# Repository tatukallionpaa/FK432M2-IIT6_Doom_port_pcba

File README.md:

Kicad project files for STM32 doom port. Software repo in https://github.com/tatukallionpaa/stm32_h743_doom_port.

Based on FK743M2-IIT6 dev board. Video is outputted via VGA and a USB keyboard is used as an input.

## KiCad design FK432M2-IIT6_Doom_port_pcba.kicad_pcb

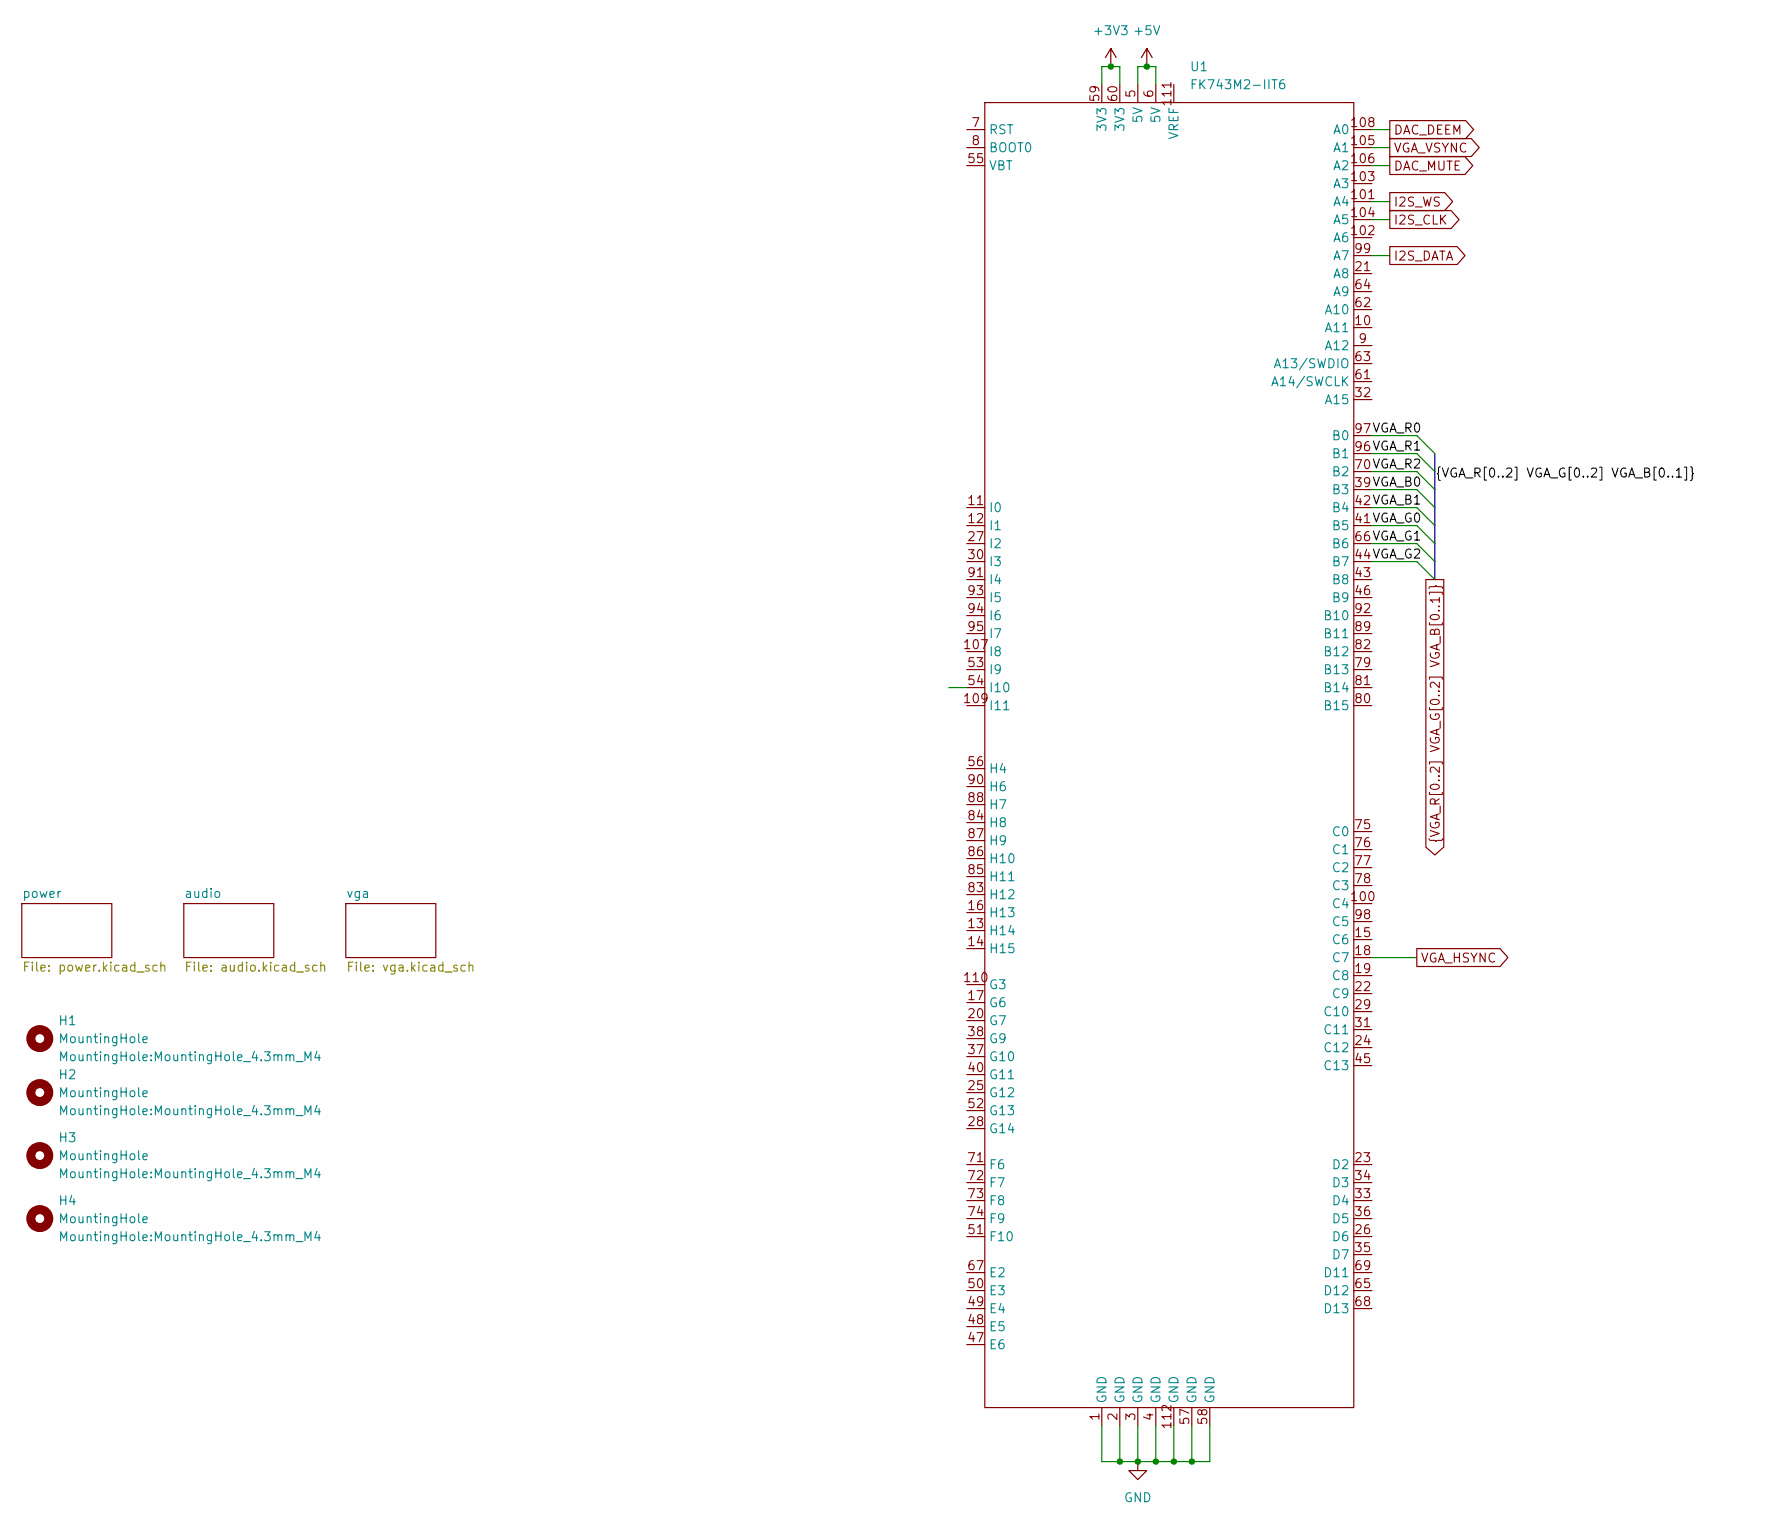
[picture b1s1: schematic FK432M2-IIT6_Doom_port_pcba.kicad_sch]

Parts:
H1, H2, H3, H4: MountingHole; MountingHole_4.3mm_M4
U1: FK743M2-IIT6; FK432M2-IIT6

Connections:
+3V3: U1.59 (3V3), U1.60 (3V3); also elsewhere on the board
+5V: U1.5 (5V), U1.6 (5V); also elsewhere on the board
DAC_DEEM: U1.108 (A0); also elsewhere on the board
DAC_MUTE: U1.106 (A2); also elsewhere on the board
GND: U1.1 (GND), U1.2 (GND), U1.3 (GND), U1.4 (GND), U1.57 (GND), U1.58 (GND), U1.112 (GND); also elsewhere on the board
I2S_CLK: U1.104 (A5); also elsewhere on the board
I2S_DATA: U1.99 (A7); also elsewhere on the board
I2S_WS: U1.101 (A4); also elsewhere on the board
VGA_B0: U1.39 (B3); also elsewhere on the board
VGA_B1: U1.42 (B4); also elsewhere on the board
VGA_G0: U1.41 (B5); also elsewhere on the board
VGA_G1: U1.66 (B6); also elsewhere on the board
VGA_G2: U1.44 (B7); also elsewhere on the board
VGA_HSYNC: U1.18 (C7); also elsewhere on the board
VGA_R0: U1.97 (B0); also elsewhere on the board
VGA_R1: U1.96 (B1); also elsewhere on the board
VGA_R2: U1.70 (B2); also elsewhere on the board
VGA_VSYNC: U1.105 (A1); also elsewhere on the board

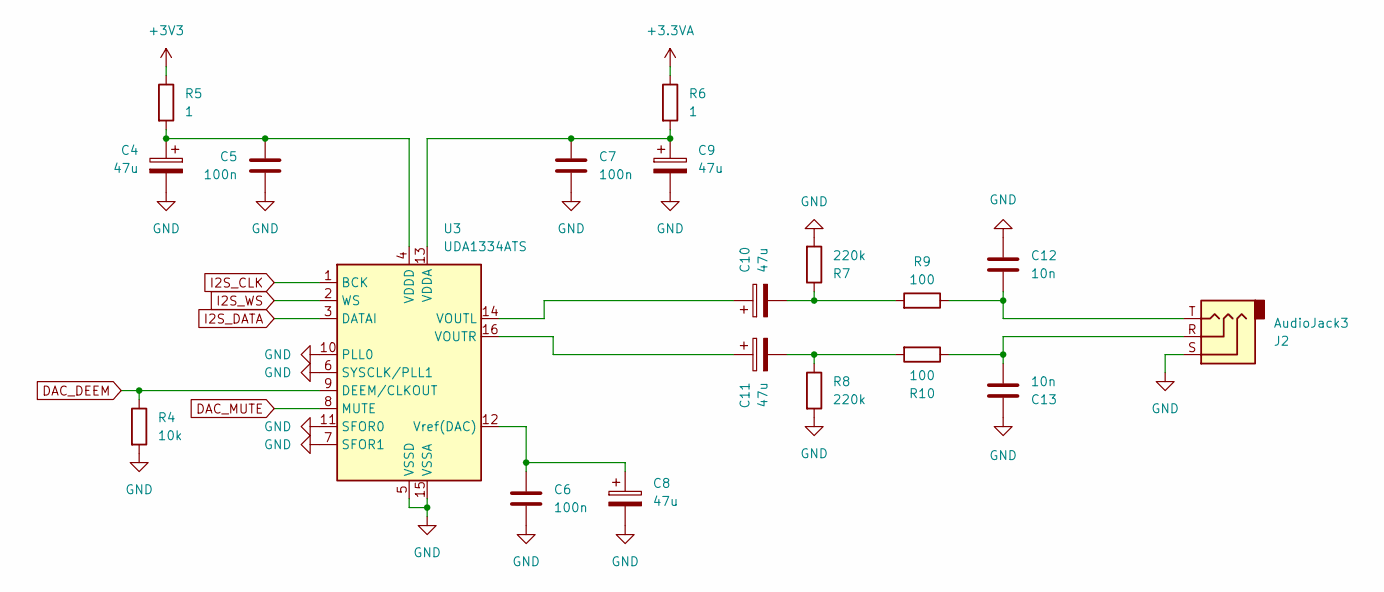
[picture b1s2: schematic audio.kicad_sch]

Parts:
C4, C8, C9, C10, C11: 47u; CP_Elec_5x5.4
C5, C6, C7: 100n; C_0805_2012Metric_Pad1.18x1.45mm_HandSolder
C12, C13: 10n; C_0805_2012Metric_Pad1.18x1.45mm_HandSolder
J2: AudioJack3; Jack_3.5mm_Lumberg_1503_07_Horizontal
R4: 10k; R_0805_2012Metric_Pad1.20x1.40mm_HandSolder
R5, R6: 1; R_0805_2012Metric_Pad1.20x1.40mm_HandSolder
R7, R8: 220k; R_0805_2012Metric_Pad1.20x1.40mm_HandSolder
R9, R10: 100; R_0805_2012Metric_Pad1.20x1.40mm_HandSolder
U3: UDA1334ATS; SSOP-16_4.4x5.2mm_P0.65mm

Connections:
+3.3VA: R6.1; also elsewhere on the board
+3V3: R5.1; also elsewhere on the board
DAC_DEEM: R4.1, U3.9 (DEEM/CLKOUT); also elsewhere on the board
DAC_MUTE: U3.8 (MUTE); also elsewhere on the board
GND: C4.2, C5.2, C6.2, C7.2, C8.2, C9.2, C12.1, C13.1, J2.S, R4.2, R7.2, R8.2, U3.5 (VSSD), U3.6 (SYSCLK/PLL1), U3.7 (SFOR1), U3.10 (PLL0), U3.11 (SFOR0), U3.15 (VSSA); also elsewhere on the board
I2S_CLK: U3.1 (BCK); also elsewhere on the board
I2S_DATA: U3.3 (DATAI); also elsewhere on the board
I2S_WS: U3.2 (WS); also elsewhere on the board
unnamed: C10.2, R7.1, R9.2
unnamed: C11.2, R8.1, R10.2
unnamed: C12.2, J2.T, R9.1
unnamed: C13.2, J2.R, R10.1
unnamed: C7.1, C9.1, R6.2, U3.13 (VDDA)
unnamed: C4.1, C5.1, R5.2, U3.4 (VDDD)
unnamed: C10.1, U3.14 (VOUTL)
unnamed: C11.1, U3.16 (VOUTR)
unnamed: C6.1, C8.1, U3.12 (Vref(DAC))

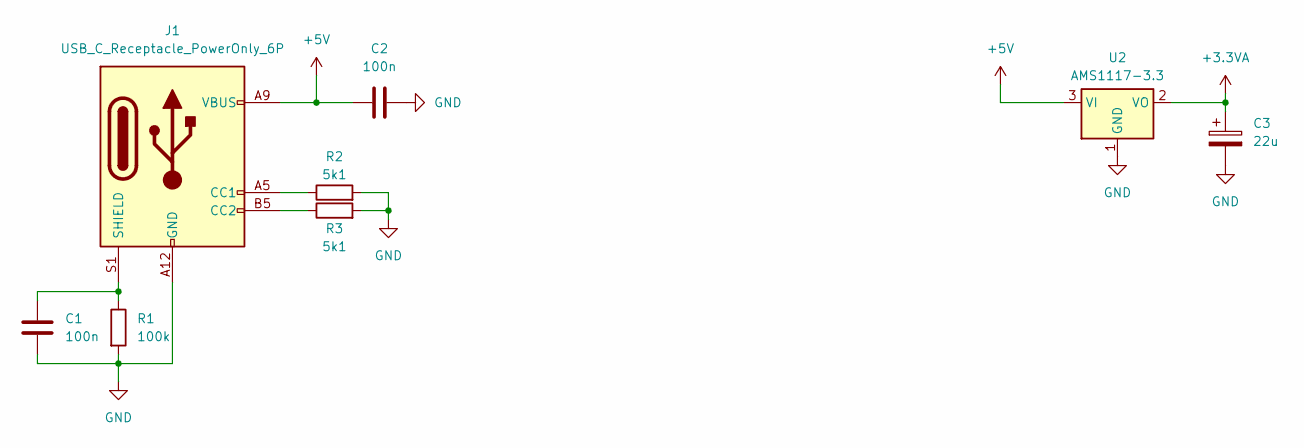
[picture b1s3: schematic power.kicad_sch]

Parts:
C1, C2: 100n; C_0805_2012Metric_Pad1.18x1.45mm_HandSolder
C3: 22u; CP_Elec_4x5.4
J1: USB_C_Receptacle_PowerOnly_6P; USB_C_Receptacle_GCT_USB4125-xx-x_6P_TopMnt_Horizontal
R1: 100k; R_0805_2012Metric_Pad1.20x1.40mm_HandSolder
R2, R3: 5k1; R_0805_2012Metric_Pad1.20x1.40mm_HandSolder
U2: AMS1117-3.3; SOT-223-3_TabPin2

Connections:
+3.3VA: C3.1, U2.2 (VO); also elsewhere on the board
+5V: C2.1, J1.A9 (VBUS), J1.B9 (VBUS), U2.3 (VI); also elsewhere on the board
GND: C1.2, C2.2, C3.2, J1.A12 (GND), J1.B12 (GND), R1.2, R2.2, R3.2, U2.1 (GND); also elsewhere on the board
unnamed: J1.A5 (CC1), R2.1
unnamed: J1.B5 (CC2), R3.1
unnamed: C1.1, J1.S1 (SHIELD), R1.1

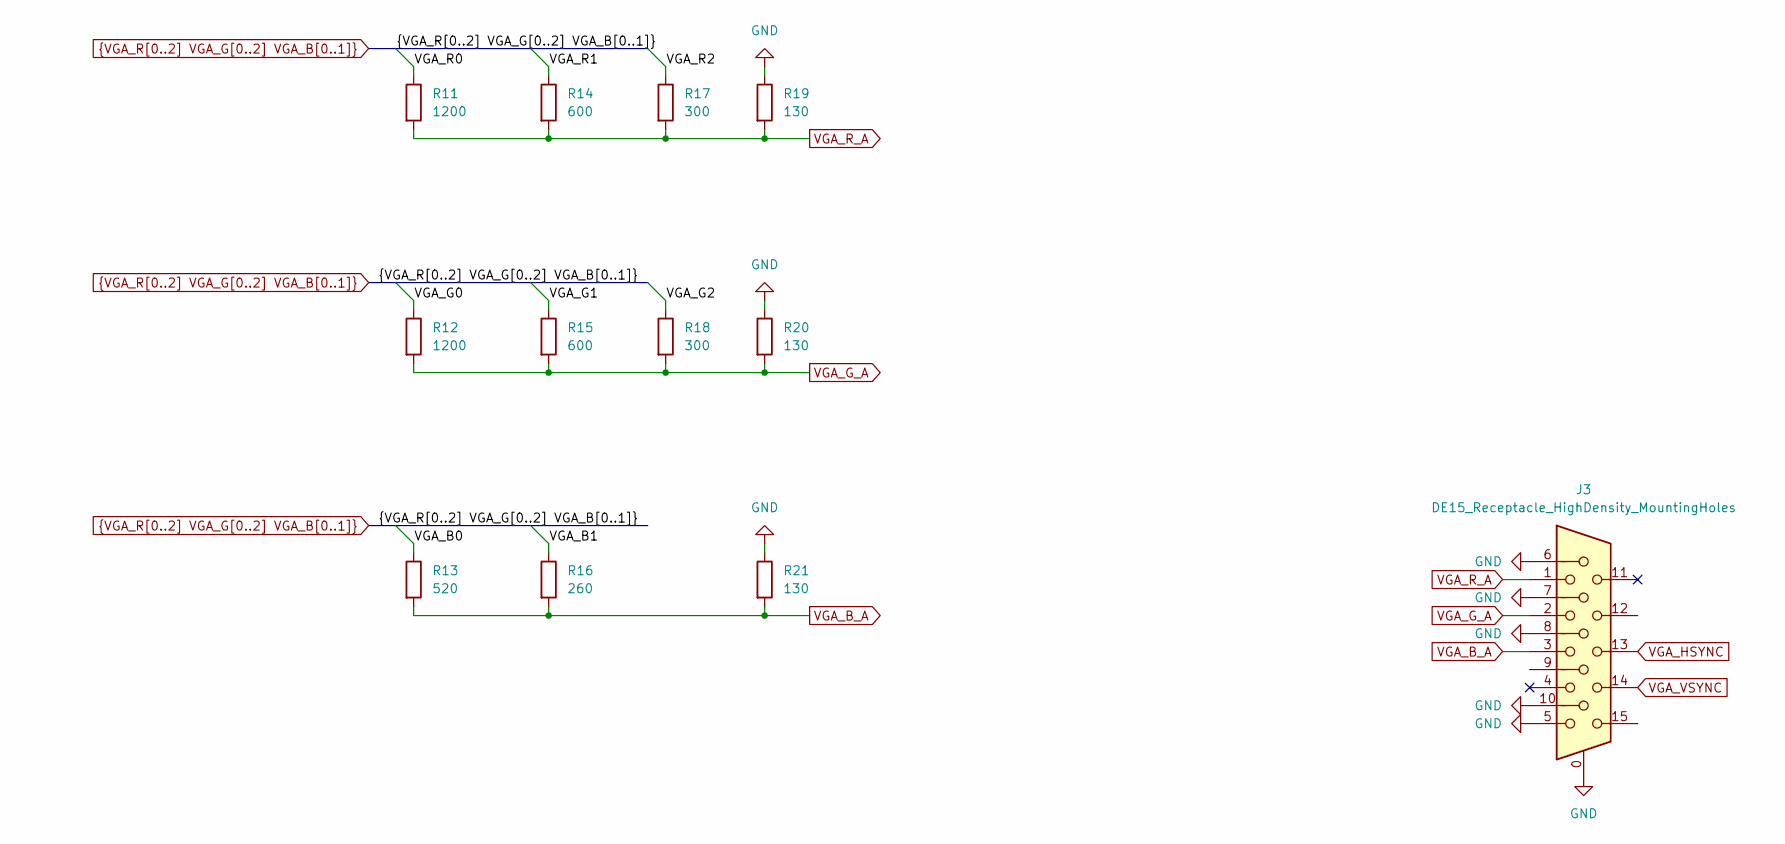
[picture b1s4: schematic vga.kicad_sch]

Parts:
J3: DE15_Receptacle_HighDensity_MountingHoles; DSUB-15-HD_Female_Horizontal_P2.29x1.98mm_EdgePinOffset3.03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
R11, R12: 1200; R_0805_2012Metric_Pad1.20x1.40mm_HandSolder
R13: 520; R_0805_2012Metric_Pad1.20x1.40mm_HandSolder
R14, R15: 600; R_0805_2012Metric_Pad1.20x1.40mm_HandSolder
R16: 260; R_0805_2012Metric_Pad1.20x1.40mm_HandSolder
R17, R18: 300; R_0805_2012Metric_Pad1.20x1.40mm_HandSolder
R19, R20, R21: 130; R_0805_2012Metric_Pad1.20x1.40mm_HandSolder

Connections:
GND: J3.0, J3.5, J3.6, J3.7, J3.8, J3.10, R19.1, R20.1, R21.1; also elsewhere on the board
VGA_B0: R13.1; also elsewhere on the board
VGA_B1: R16.1; also elsewhere on the board
VGA_B_A: J3.3, R13.2, R16.2, R21.2
VGA_G0: R12.1; also elsewhere on the board
VGA_G1: R15.1; also elsewhere on the board
VGA_G2: R18.1; also elsewhere on the board
VGA_G_A: J3.2, R12.2, R15.2, R18.2, R20.2
VGA_HSYNC: J3.13; also elsewhere on the board
VGA_R0: R11.1; also elsewhere on the board
VGA_R1: R14.1; also elsewhere on the board
VGA_R2: R17.1; also elsewhere on the board
VGA_R_A: J3.1, R11.2, R14.2, R17.2, R19.2
VGA_VSYNC: J3.14; also elsewhere on the board

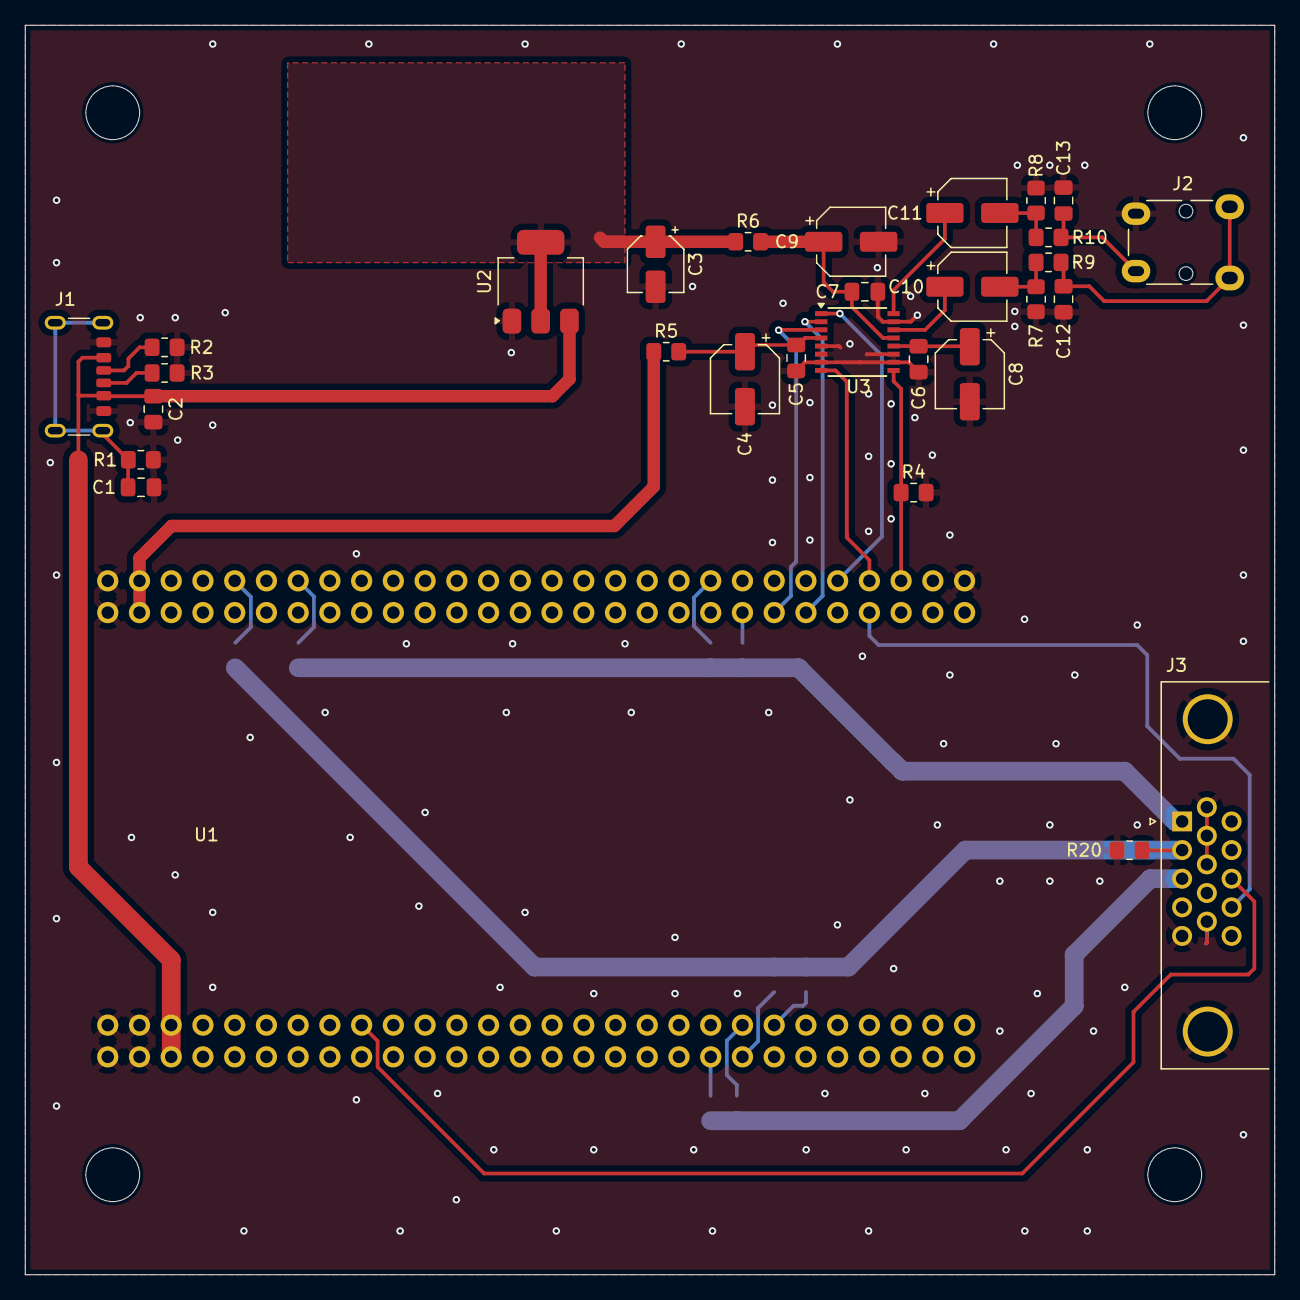
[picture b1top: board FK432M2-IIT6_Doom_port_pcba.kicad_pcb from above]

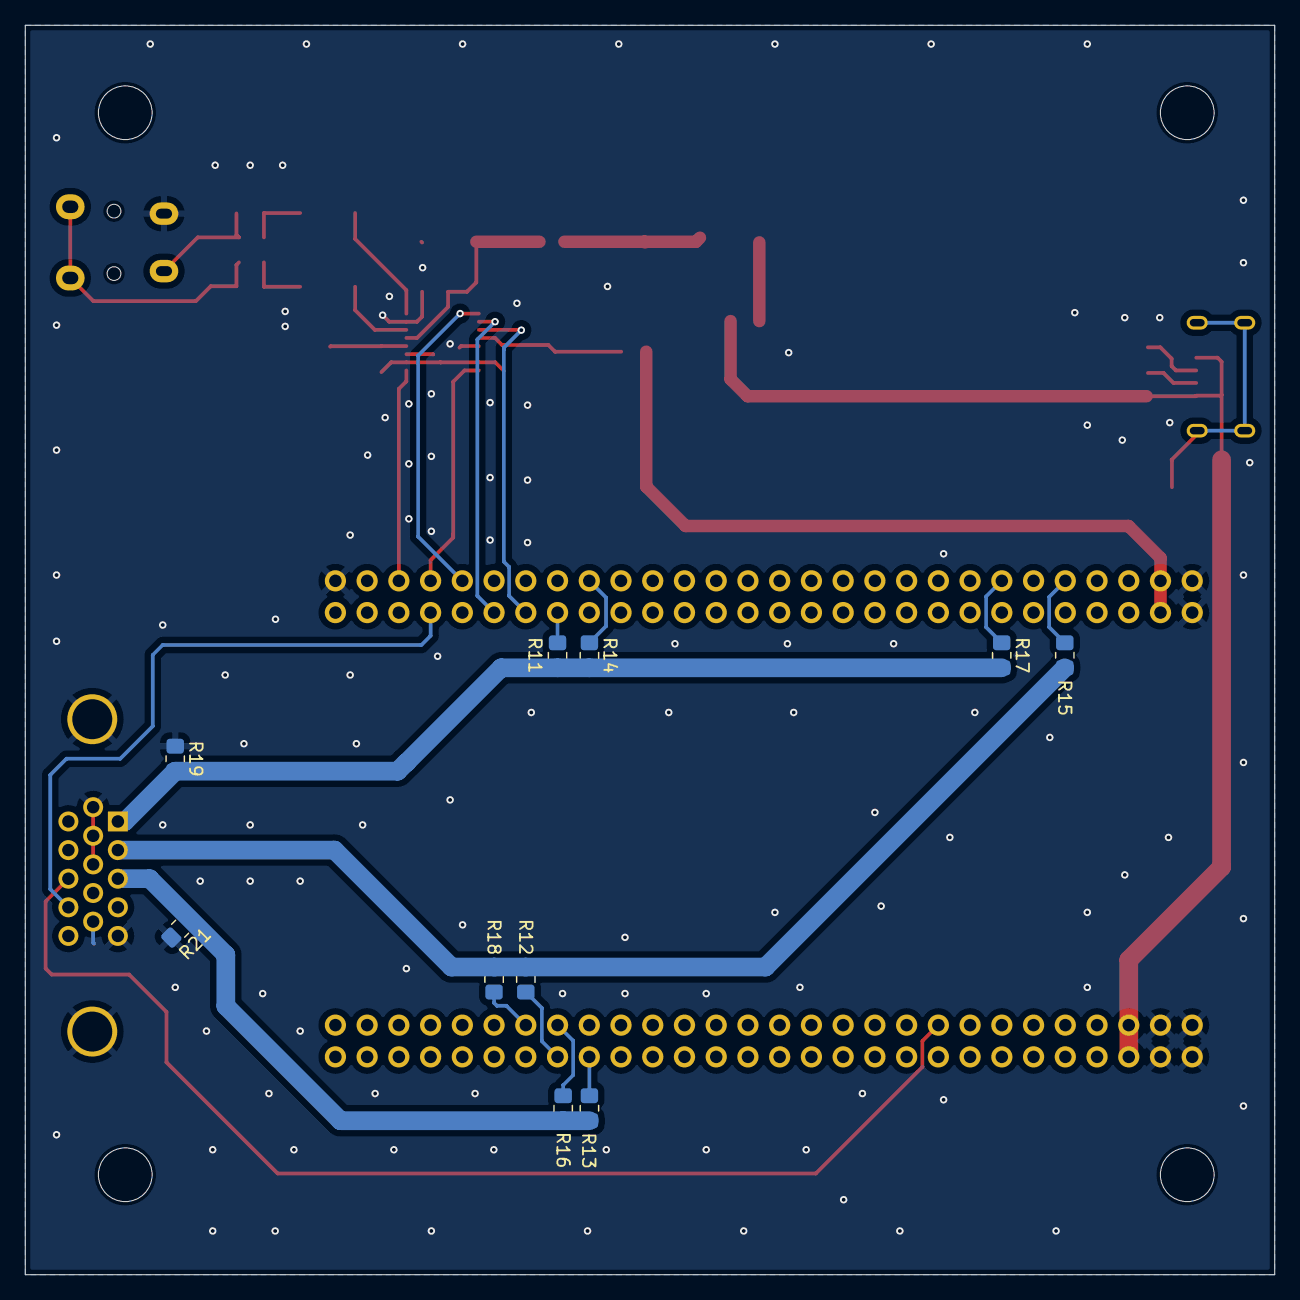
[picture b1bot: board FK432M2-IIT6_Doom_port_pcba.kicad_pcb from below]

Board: 2 copper layers, 100.0 x 100.0 mm, 44 parts (10 on the bottom side), 34 nets.

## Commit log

2025-09-29 First rev of doom port pcba. 8-bit rgb color
